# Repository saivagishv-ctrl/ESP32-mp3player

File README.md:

This is my first ever pcb project, I used AI to ask questions about the KiCAD ui, and to recommend me a specifec model number when i gave it constraints for what i wanted in a component, like the charging module for the battery with passthrough and voltage detection
breakdown of cost: jlcpcb manufacturing total:35 dollar (so much shipping cost and no way to cancel it, not even with other companies)
parts cost on jlcpcb: 25ish dollars without shipping

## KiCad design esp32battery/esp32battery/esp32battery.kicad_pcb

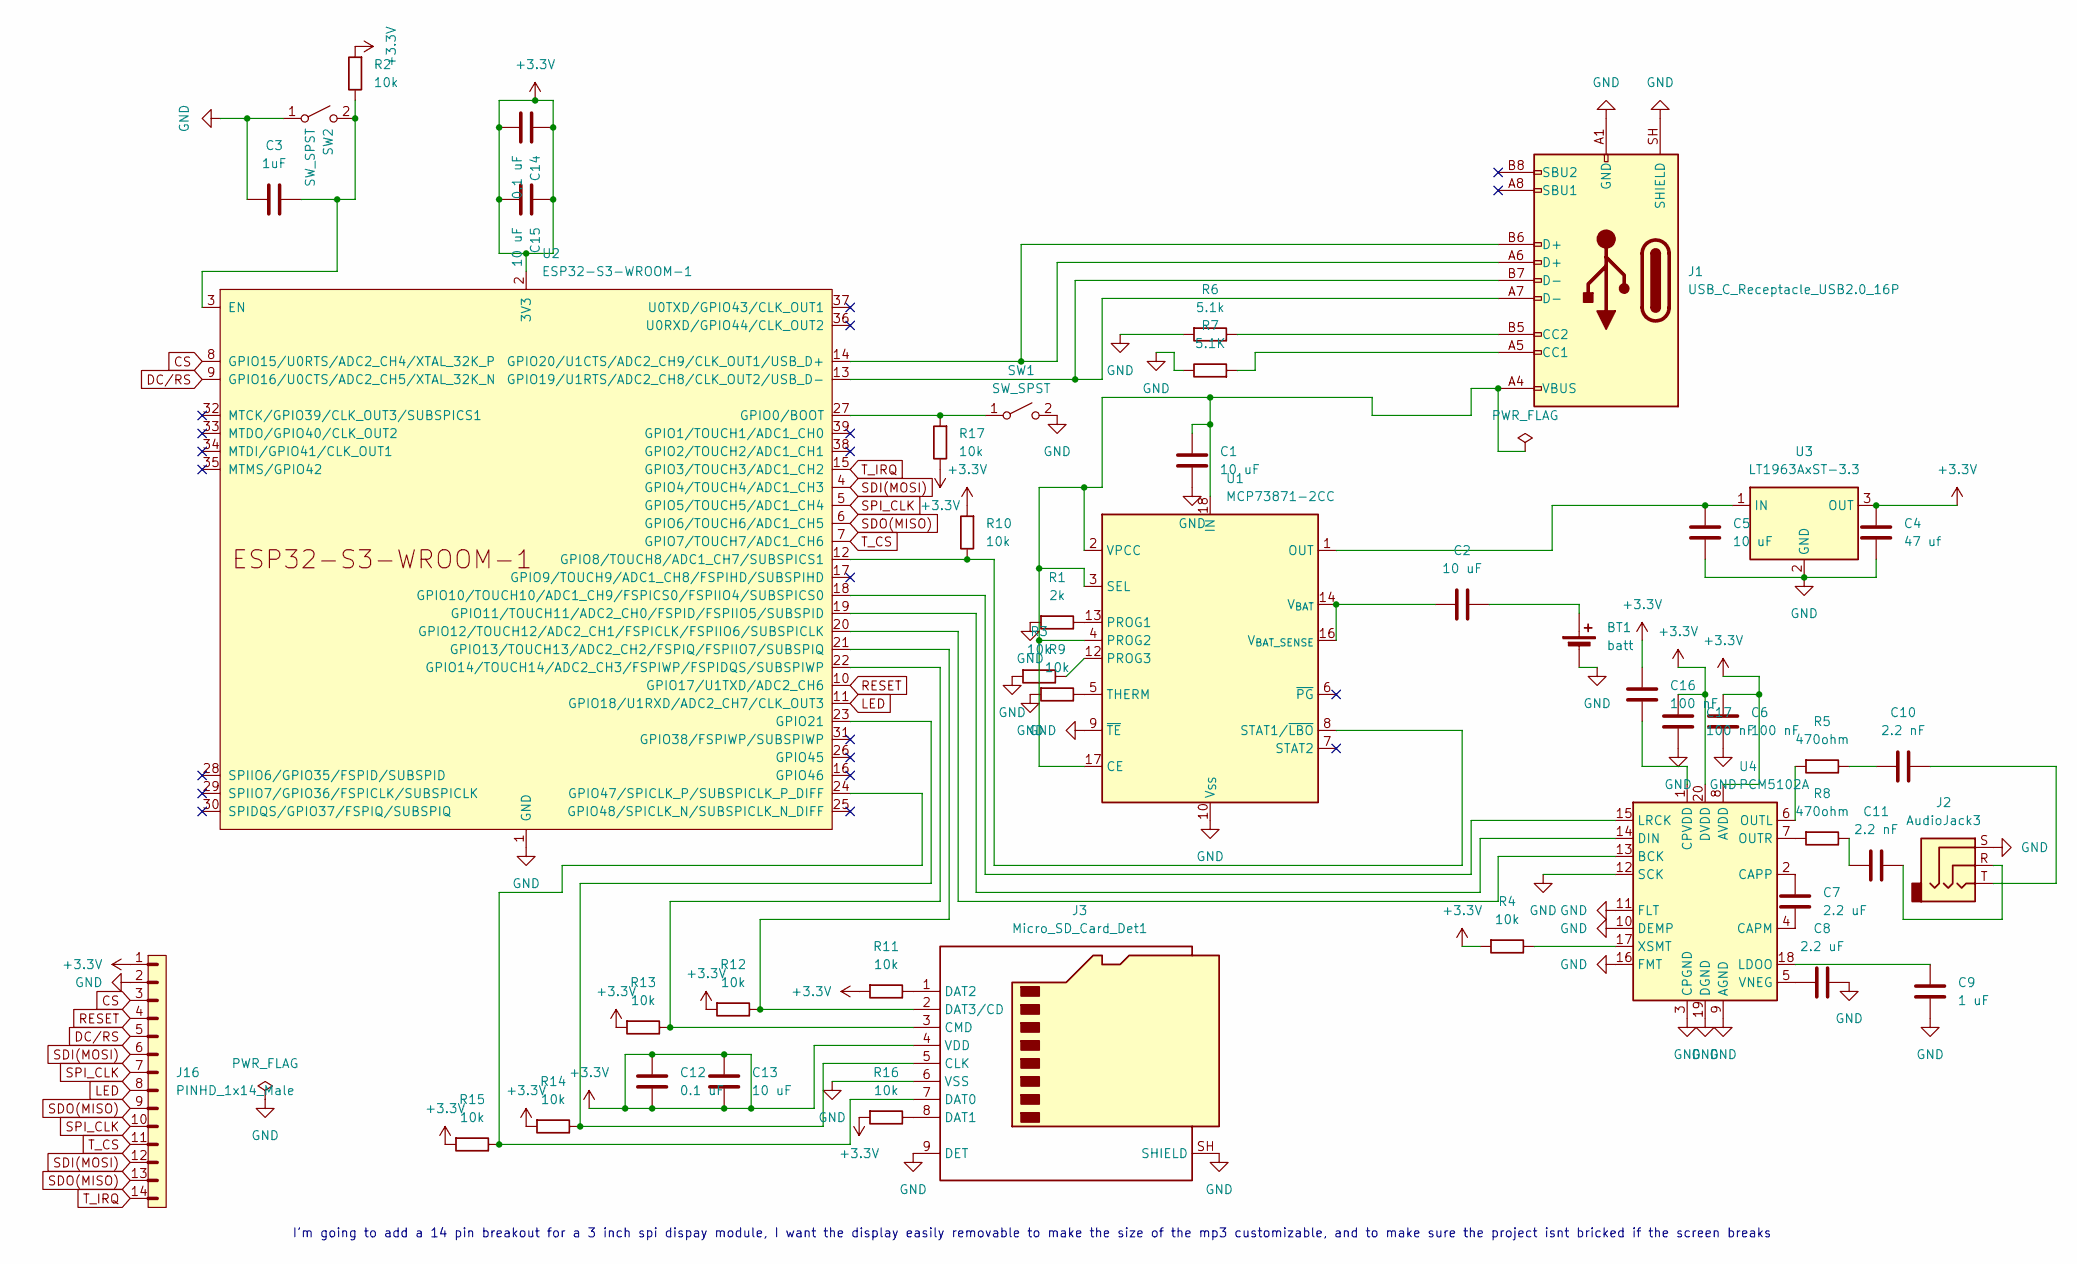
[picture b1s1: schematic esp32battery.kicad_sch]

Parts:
BT1: batt; JST_PH_S2B-PH-K_1x02_P2.00mm_Horizontal
C1, C2, C5, C13, C15: 10 uF; C_0805_2012Metric_Pad1.18x1.45mm_HandSolder
C3: 1uF; C_0805_2012Metric_Pad1.18x1.45mm_HandSolder
C4: 47 uf; C_0805_2012Metric_Pad1.18x1.45mm_HandSolder
C6, C16, C17: 100 nF; C_0805_2012Metric_Pad1.18x1.45mm_HandSolder
C7, C8: 2.2 uF; C_0805_2012Metric_Pad1.18x1.45mm_HandSolder
C9: 1 uF; C_0805_2012Metric_Pad1.18x1.45mm_HandSolder
C10, C11: 2.2 nF; C_0805_2012Metric_Pad1.18x1.45mm_HandSolder
C12, C14: 0.1 uF; C_0805_2012Metric_Pad1.18x1.45mm_HandSolder
J1: USB_C_Receptacle_USB2.0_16P; USB_C_Receptacle_GCT_USB4105-xx-A_16P_TopMnt_Horizontal
J2: AudioJack3; Jack_3.5mm_CUI_SJ1-3533NG_Horizontal
J3: Micro_SD_Card_Det1; microSD_HC_Molex_104031-0811
J16: PINHD_1x14_Male; PinHeader_1x14_P2.54mm_Vertical
R1: 2k; R_Axial_DIN0207_L6.3mm_D2.5mm_P10.16mm_Horizontal
R2, R3, R4, R9, R10, R11, R12, R13, R14, R15, R16, R17: 10k; R_Axial_DIN0207_L6.3mm_D2.5mm_P10.16mm_Horizontal
R5, R8: 470ohm; R_Axial_DIN0207_L6.3mm_D2.5mm_P10.16mm_Horizontal
R6: 5.1k; R_Axial_DIN0207_L6.3mm_D2.5mm_P10.16mm_Horizontal
R7: 5.1K; R_Axial_DIN0207_L6.3mm_D2.5mm_P10.16mm_Horizontal
SW1, SW2: SW_SPST; SW_Push_SPST_NO_Alps_SKRK
U1: MCP73871-2CC; QFN-20-1EP_4x4mm_P0.5mm_EP2.5x2.5mm
U2: ESP32-S3-WROOM-1
U3: LT1963AxST-3.3; SOT-223-3_TabPin2
U4: PCM5102A; TSSOP-20_4.4x6.5mm_P0.65mm

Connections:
+3.3V: C4.1, C6.1, C12.1, C12.2, C13.1, C13.2, C14.1, C14.2, C15.1, C15.2, C16.1, C17.1, J3.4 (VDD), J16.1, R2.1, R4.1, R10.1, R11.1, R12.1, R13.1, R14.1, R15.1, R16.1, R17.2, U2.2 (3V3), U3.3 (OUT), U4.8 (AVDD), U4.20 (DVDD)
CS: J16.3, U2.8 (GPIO15/U0RTS/ADC2_CH4/XTAL_32K_P)
DC/RS: J16.5, U2.9 (GPIO16/U0CTS/ADC2_CH5/XTAL_32K_N)
GND: BT1.2 (-), C1.2, C3.2, C4.2, C5.2, C6.2, C8.1, C9.2, C17.2, J1.A1 (GND), J1.A12 (GND), J1.B1 (GND), J1.B12 (GND), J1.SH (SHIELD), J2.S, J3.6 (VSS), J3.9 (DET), J3.SH (SHIELD), J16.2, R1.1, R3.1, R6.1, R7.2, R9.1, SW1.2 (B), SW2.1 (A), U1.9 (~TE), U1.10 (V_{SS}), U1.11 (V_{SS}), U1.21 (V_{SS}), U2.1 (GND), U2.40 (GND), U2.41 (GND), U3.2 (GND), U4.3 (CPGND), U4.9 (AGND), U4.10 (DEMP), U4.11 (FLT), U4.12 (SCK), U4.16 (FMT), U4.19 (DGND)
LED: J16.8, U2.11 (GPIO18/U1RXD/ADC2_CH7/CLK_OUT3)
unnamed: BT1.1 (+), C2.1
unnamed: C10.1, J2.T
unnamed: C10.2, R5.2
unnamed: C11.1, R8.2
unnamed: C11.2, J2.R
unnamed: J1.A5 (CC1), R7.1
unnamed: J1.B5 (CC2), R6.2
unnamed: J3.5 (CLK), R14.2, U2.23 (GPIO21)
unnamed: J3.3 (CMD), R13.2, U2.22 (GPIO14/TOUCH14/ADC2_CH3/FSPIWP/FSPIDQS/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)
unnamed: J3.7 (DAT0), R15.2, U2.24 (GPIO47/SPICLK_P/SUBSPICLK_P_DIFF)
unnamed: J3.8 (DAT1), R16.2
unnamed: J3.1 (DAT2), R11.2
unnamed: J3.2 (DAT3/CD), R12.2, U2.21 (GPIO13/TOUCH13/ADC2_CH2/FSPIQ/FSPIIO7/S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)
unnamed: R17.1, SW1.1 (A), U2.27 (GPIO0/BOOT)
unnamed: C3.1, R2.2, SW2.2 (B), U2.3 (EN)
unnamed: C1.1, J1.A4 (VBUS), J1.A9 (VBUS), J1.B4 (VBUS), J1.B9 (VBUS), U1.2 (VPCC), U1.3 (SEL), U1.4 (PROG2), U1.17 (CE), U1.18 (IN), U1.19 (IN)
unnamed: R1.2, U1.13 (PROG1)
unnamed: R3.2, U1.12 (PROG3)
unnamed: R10.2, U1.8 (STAT1/~LBO), U2.12 (GPIO8/TOUCH8/ADC1_CH7/SUBSPICS1)
unnamed: R9.2, U1.5 (THERM)
unnamed: C2.2, U1.14 (V_{BAT}), U1.15 (V_{BAT}), U1.16 (V_{BAT_SENSE})
unnamed: U2.18 (GPIO10/TOUCH10/ADC1_CH9/FSPICS0/FSPIIO4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), U4.15 (LRCK)
unnamed: U2.19 (GPIO11/TOUCH11/ADC2_CH0/FSPID/FSPIIO5/S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), U4.14 (DIN)
unnamed: U2.20 (GPIO12/TOUCH12/ADC2_CH1/FSPICLK/FSPIIO6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), U4.13 (BCK)
unnamed: J1.A7 (D-), J1.B7 (D-), U2.13 (GPIO19/U1RTS/ADC2_CH8/CLK_OUT2/USB_D-)
unnamed: J1.A6 (D+), J1.B6 (D+), U2.14 (GPIO20/U1CTS/ADC2_CH9/CLK_OUT1/USB_D+)
unnamed: C5.1, U1.1 (OUT), U1.20 (OUT), U3.1 (IN)
unnamed: C7.2, U4.4 (CAPM)
unnamed: C7.1, U4.2 (CAPP)
unnamed: C16.2, U4.1 (CPVDD)
unnamed: C9.1, U4.18 (LDOO)
unnamed: R5.1, U4.6 (OUTL)
unnamed: R8.1, U4.7 (OUTR)
unnamed: C8.2, U4.5 (VNEG)
unnamed: R4.2, U4.17 (XSMT)
RESET: J16.4, U2.10 (GPIO17/U1TXD/ADC2_CH6)
SDI(MOSI): J16.6, J16.12, U2.4 (GPIO4/TOUCH4/ADC1_CH3)
SDO(MISO): J16.9, J16.13, U2.6 (GPIO6/TOUCH6/ADC1_CH5)
SPI_CLK: J16.7, J16.10, U2.5 (GPIO5/TOUCH5/ADC1_CH4)
T_CS: J16.11, U2.7 (GPIO7/TOUCH7/ADC1_CH6)
T_IRQ: J16.14, U2.15 (GPIO3/TOUCH3/ADC1_CH2)

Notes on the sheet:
I'm going to add a 14 pin breakout for a 3 inch spi dispay module, I want the display easily removable to make the size of the mp3 customizable, and to make sure the project isnt bricked if the screen breaks

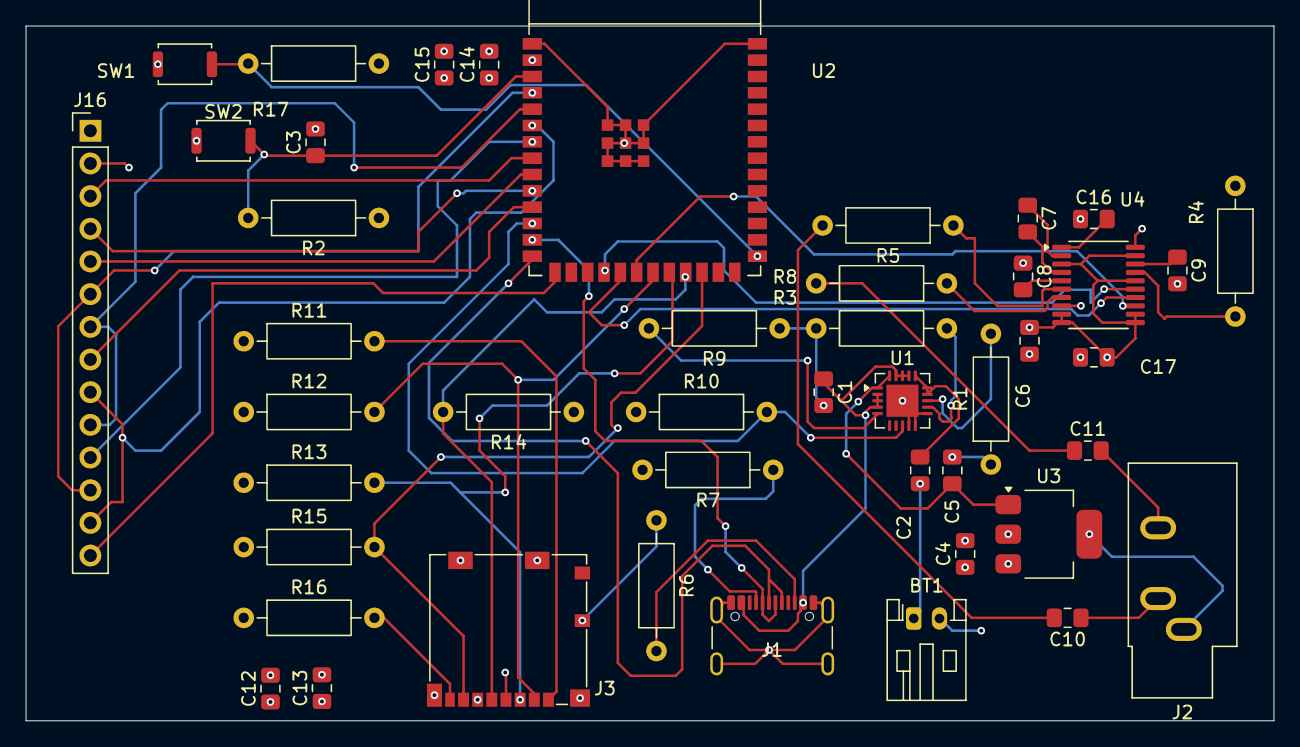
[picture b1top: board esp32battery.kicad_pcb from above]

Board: 4 copper layers, 97.0 x 54.0 mm, 45 parts (0 on the bottom side), 46 nets.
